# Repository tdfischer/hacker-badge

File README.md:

# Hacker Soldering Badge

A badge that can teach aspiring hackers how to solder!

Ingredients:

- 1 CR1220 Battery
- 1 CR1220 Battery holder
- 6 LEDs

Designed at Noisebridge by Torrie Fischer <tdfischer@hackerbots.net>.

Released under v1.2 of the CERN Open Hardware License.

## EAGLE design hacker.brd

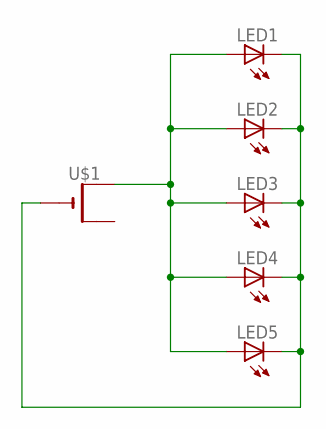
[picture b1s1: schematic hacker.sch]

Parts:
LED1, LED2, LED3, LED4, LED5: LED5MM
U$1: CR1220THM; CR1220-THM

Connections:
unnamed: LED1.A, LED2.A, LED3.A, LED4.A, LED5.A, U$1.+1 (+)
unnamed: LED1.K (C), LED2.K (C), LED3.K (C), LED4.K (C), LED5.K (C), U$1.-

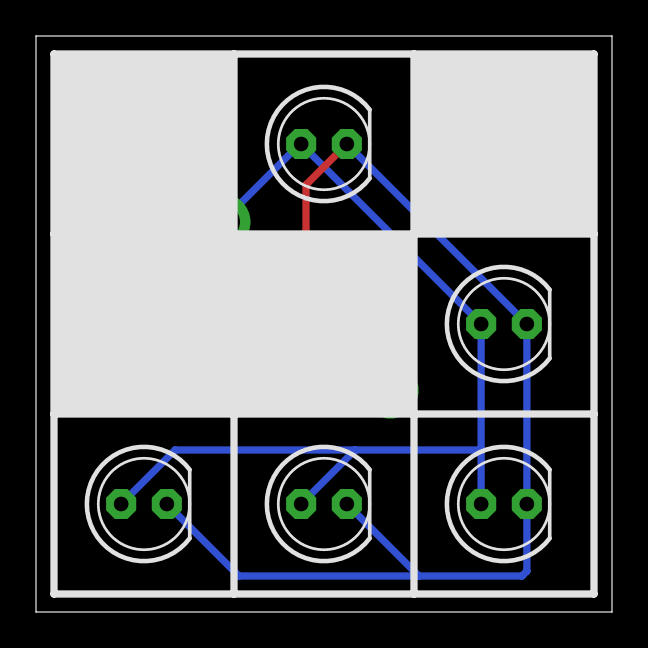
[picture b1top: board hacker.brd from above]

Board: 2 copper layers, 32.0 x 32.0 mm, 6 parts (1 on the bottom side), 2 nets.

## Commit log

2015-05-26 docs++
